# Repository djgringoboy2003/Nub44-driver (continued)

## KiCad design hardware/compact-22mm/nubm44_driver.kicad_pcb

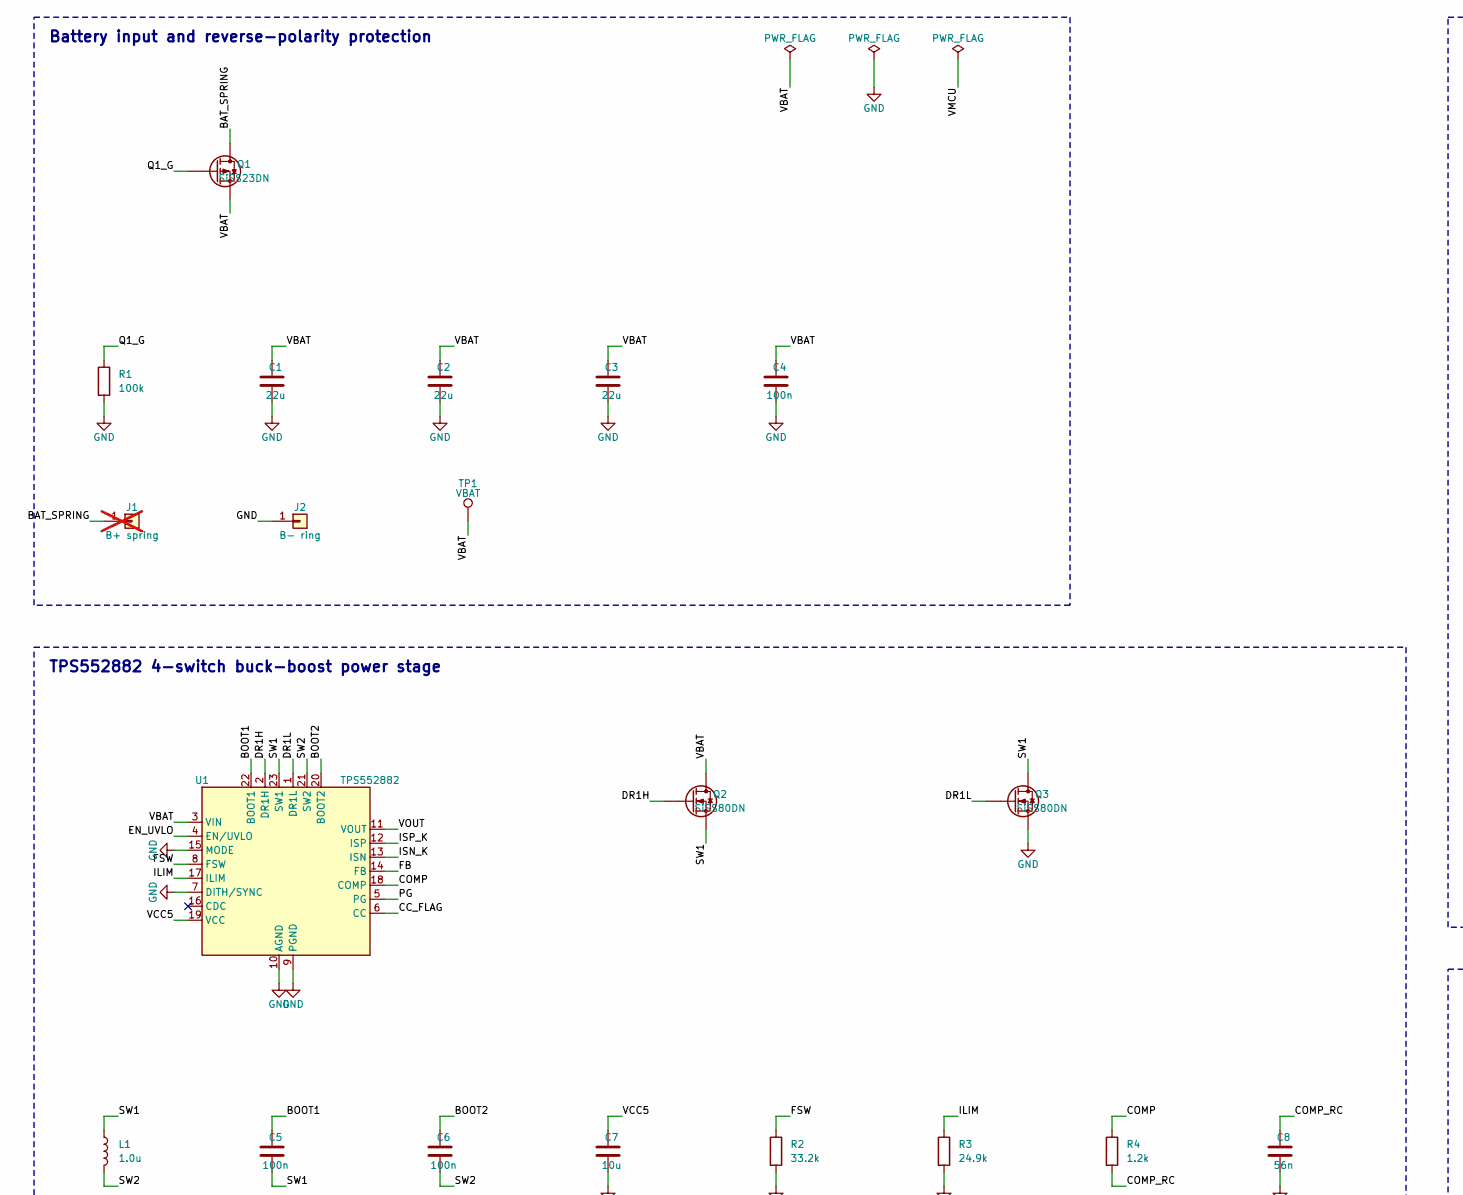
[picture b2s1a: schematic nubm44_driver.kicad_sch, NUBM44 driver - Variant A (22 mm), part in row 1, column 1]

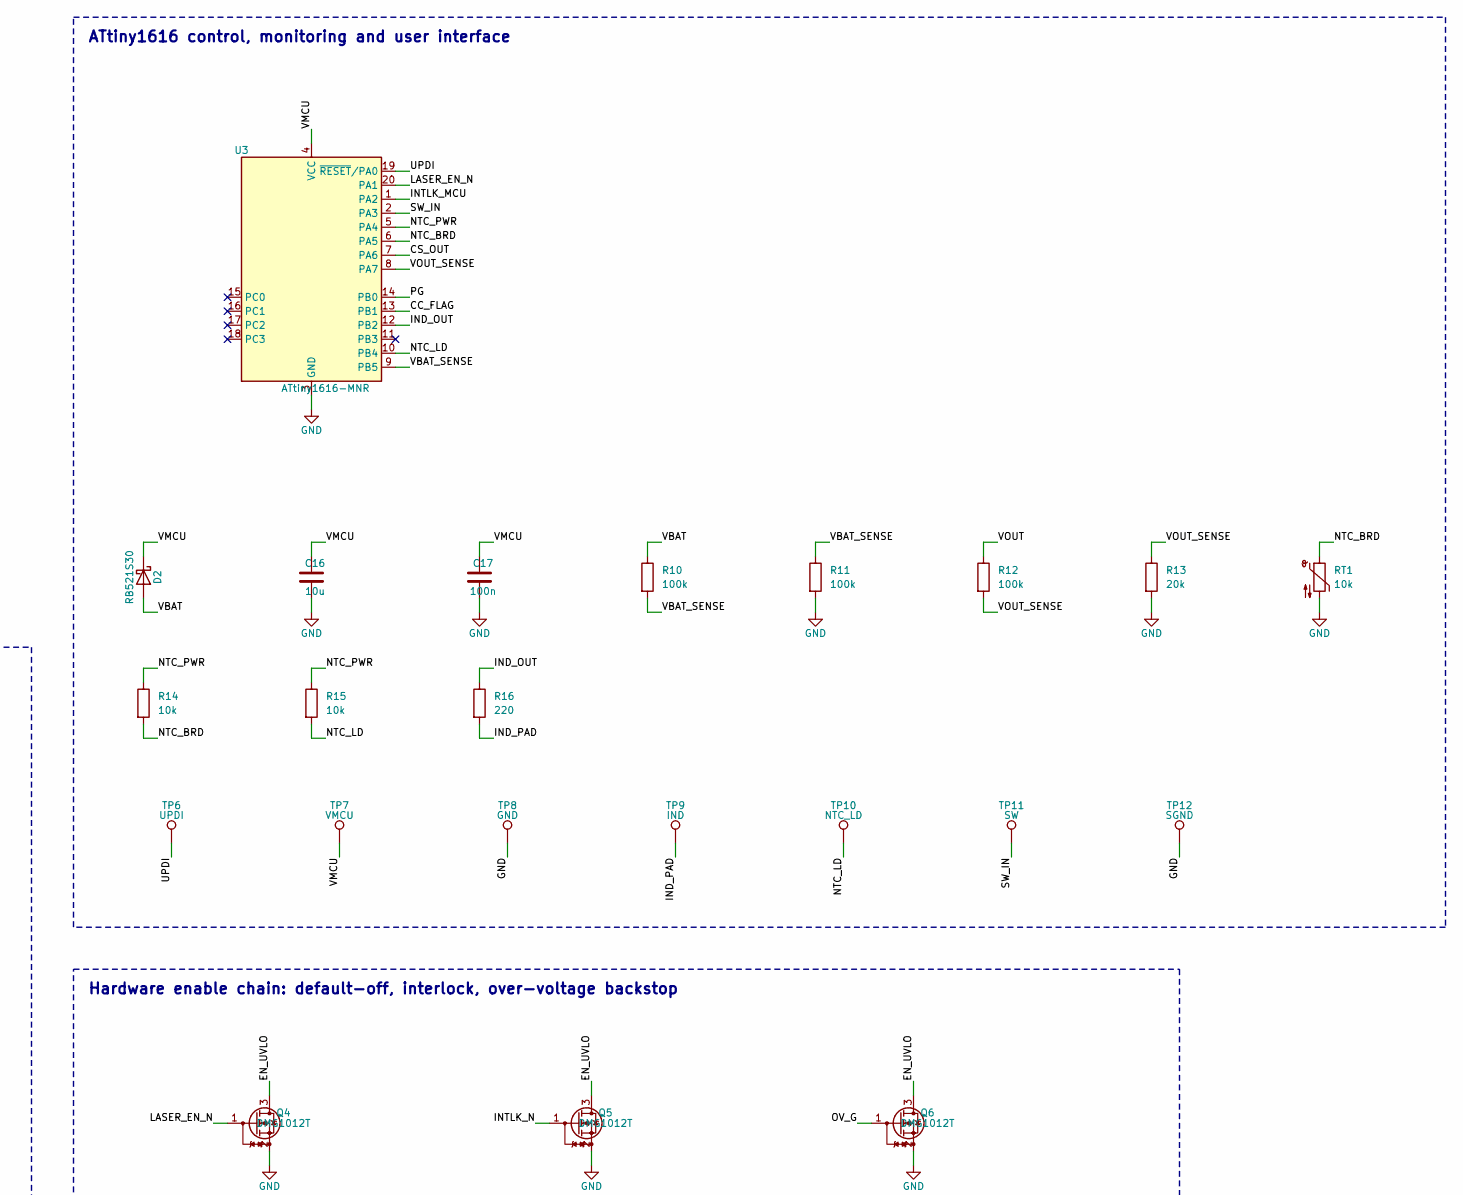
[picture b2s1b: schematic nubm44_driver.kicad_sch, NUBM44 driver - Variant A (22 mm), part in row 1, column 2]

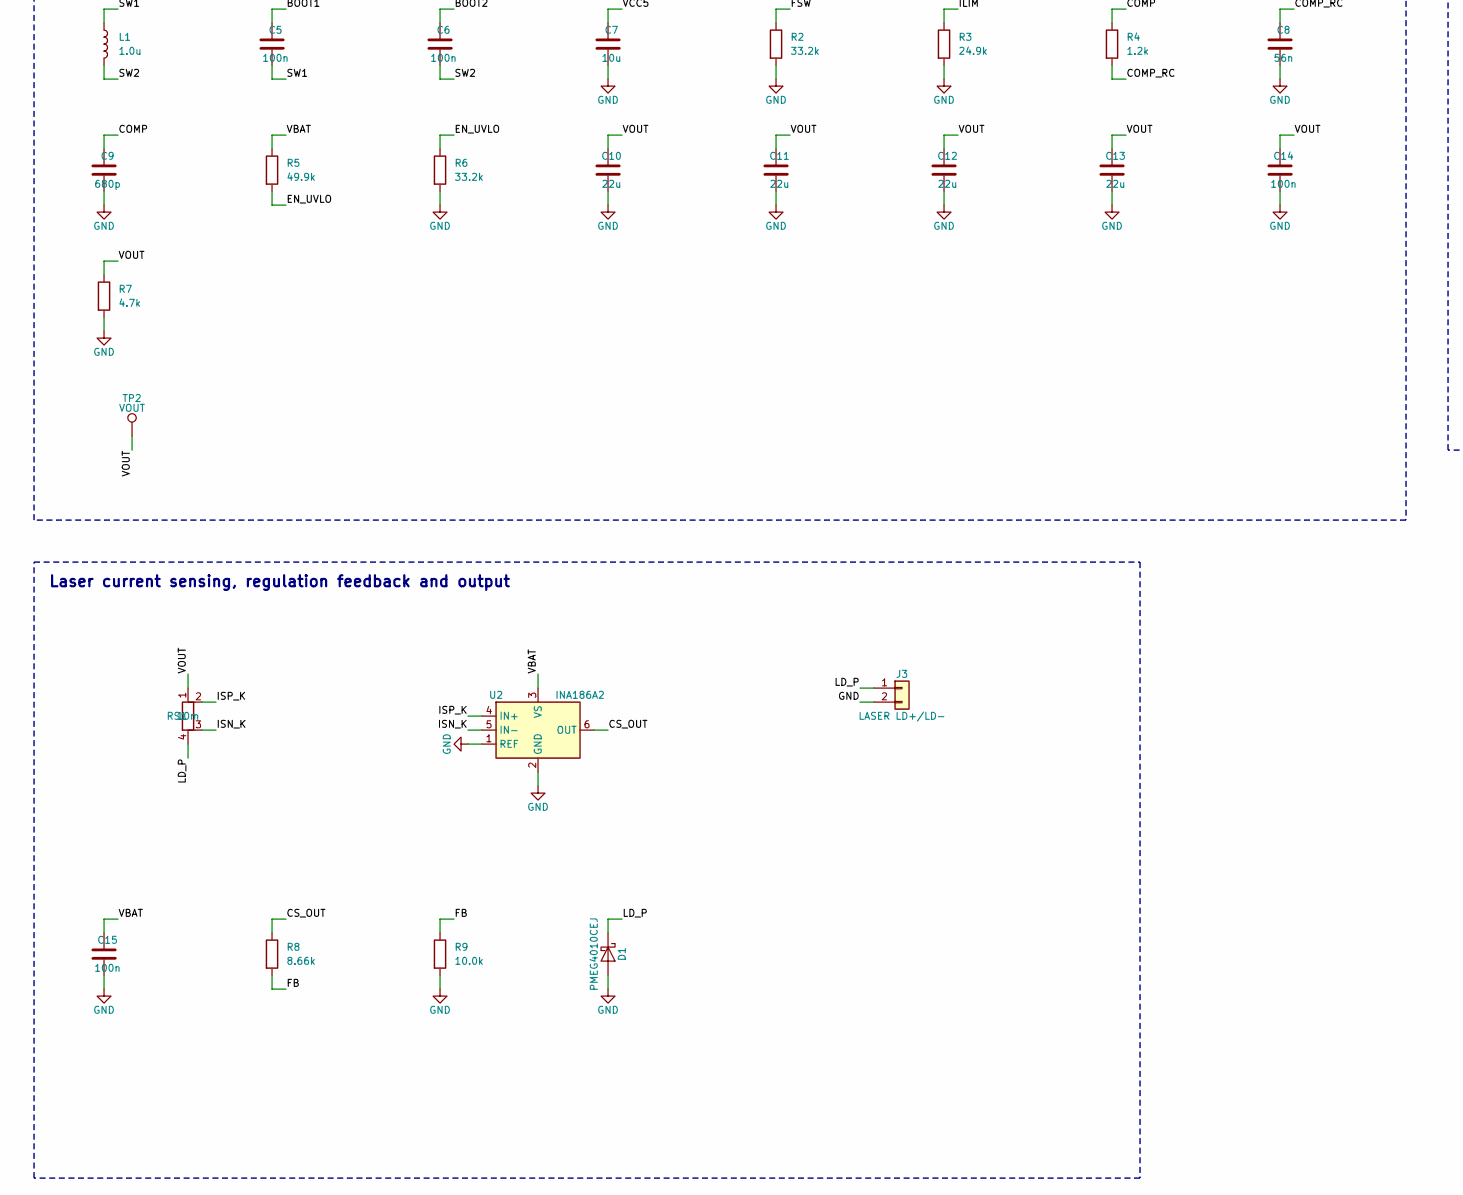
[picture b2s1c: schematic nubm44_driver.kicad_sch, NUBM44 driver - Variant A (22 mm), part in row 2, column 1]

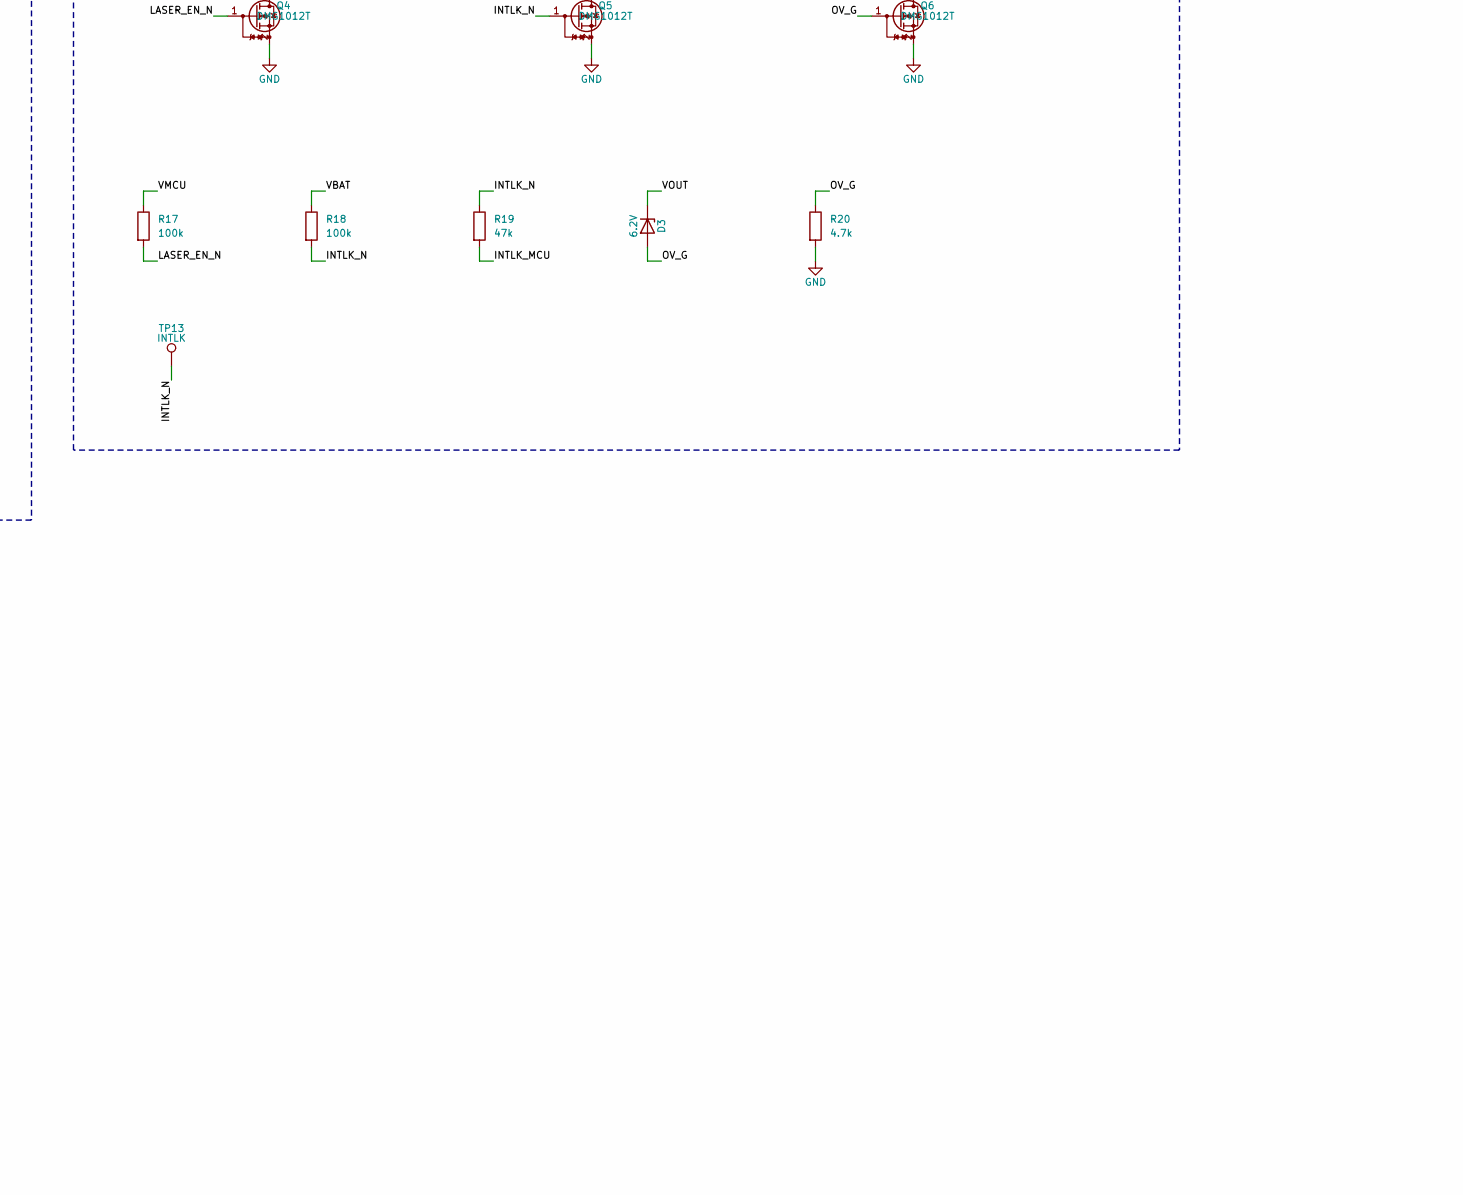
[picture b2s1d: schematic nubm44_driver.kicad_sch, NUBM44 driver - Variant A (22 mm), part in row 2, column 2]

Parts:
C1, C2, C3, C10, C11, C12, C13: 22u; C_0805_2012Metric; MPN CL21A226MOQNNNE
C4, C5, C6, C14, C15, C17: 100n; C_0201_0603Metric; MPN GRM033R61A104KE15D
C7, C16: 10u; C_0603_1608Metric; MPN CL10A106KP8NNNC
C8: 56n; C_0402_1005Metric; MPN CL05B563KO5NNNC
C9: 680p; C_0201_0603Metric; MPN GRM0335C1H681JA01D
D1: PMEG4010CEJ; D_SOD-323F; MPN PMEG4010CEJ,115
D2: RB521S30; D_SOD-523; MPN RB521S30T1G
D3: 6.2V; D_SOD-523; MPN BZX585-C6V2
J1: B+ spring; Contact_Spring_Pad_D5.0mm; MPN UNKNOWN; not fitted
J2: B- ring; Contact_Ring_R10.20_W0.80mm
J3: LASER LD+/LD-; Laser_Pads_2x_PTH_P3.5mm_D1.1mm
L1: 1.0u; L_Coilcraft_XAL5030-XXX; MPN XGL5030-102MEC
Q1: SiSS23DN; Vishay_PowerPAK_1212-8_Single; MPN SISS23DN-T1-GE3
Q2, Q3: SiSS80DN; Vishay_PowerPAK_1212-8_Single; MPN SISS80DN-T1-GE3
Q4, Q5, Q6: DMG1012T; SOT-523; MPN DMG1012T-7
R1, R10, R11, R12, R17, R18: 100k; R_0201_0603Metric; MPN RC0201FR-07100KL
R2, R6: 33.2k; R_0201_0603Metric; MPN RC0201FR-0733K2L
R3: 24.9k; R_0201_0603Metric; MPN RC0201FR-0724K9L
R4: 1.2k; R_0201_0603Metric; MPN RC0201FR-071K2L
R5: 49.9k; R_0201_0603Metric; MPN RC0201FR-0749K9L
R7, R20: 4.7k; R_0201_0603Metric; MPN RC0201FR-074K7L
R8: 8.66k; R_0402_1005Metric; MPN RT0402BRD078K66L
R9: 10.0k; R_0402_1005Metric; MPN RT0402BRD0710KL
R13: 20k; R_0201_0603Metric; MPN RC0201FR-0720KL
R14, R15: 10k; R_0201_0603Metric; MPN RC0201FR-0710KL
R16: 220; R_0201_0603Metric; MPN RC0201FR-07220RL
R19: 47k; R_0201_0603Metric; MPN RC0201FR-0747KL
RS1: 10m; R_1206_3216Metric_Kelvin; MPN MCS1632R010FER
RT1: 10k; R_0201_0603Metric; MPN NCP03XH103F05RL
TP1: VBAT; Pad_SMD_D0.8mm_B
TP2: VOUT; Pad_SMD_D0.8mm_B
TP6: UPDI; Pad_SMD_D0.8mm_B
TP7: VMCU; Pad_SMD_D0.8mm_B
TP8: GND; Pad_SMD_D0.8mm_B
TP9: IND; Pad_SMD_D1.0mm_F
TP10: NTC_LD; Pad_SMD_D1.0mm_F
TP11: SW; Pad_SMD_D1.0mm_F
TP12: SGND; Pad_SMD_D1.0mm_F
TP13: INTLK; Pad_SMD_D1.0mm_F
U1: TPS552882; TI_RPM0026A_VQFN-HR-26_4x3.5mm_P0.5mm; MPN TPS552882RPMR
U2: INA186A2; SOT-363_SC-70-6; MPN INA186A2IDCKR
U3: ATtiny1616-MNR; VQFN-20-1EP_3x3mm_P0.4mm_EP1.7x1.7mm; MPN ATTINY1616-MNR

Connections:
/BAT_SPRING: J1.1, Q1.5 (D)
/BOOT1: C5.1, U1.22 (BOOT1)
/BOOT2: C6.1, U1.20 (BOOT2)
/CC_FLAG: U1.6 (CC), U3.13 (PB1)
/COMP: C9.1, R4.1, U1.18 (COMP)
/COMP_RC: C8.1, R4.2
/CS_OUT: R8.1, U2.6 (OUT), U3.7 (PA6)
/DR1H: Q2.4 (G), U1.2 (DR1H)
/DR1L: Q3.4 (G), U1.1 (DR1L)
/EN_UVLO: Q4.3 (D), Q5.3 (D), Q6.3 (D), R5.2, R6.1, U1.4 (EN/UVLO)
/FB: R8.2, R9.1, U1.14 (FB)
/FSW: R2.1, U1.8 (FSW)
/ILIM: R3.1, U1.17 (ILIM)
/IND_OUT: R16.1, U3.12 (PB2)
/IND_PAD: R16.2, TP9.1
/INTLK_MCU: R19.2, U3.1 (PA2)
/INTLK_N: Q5.1 (G), R18.2, R19.1, TP13.1
/ISN_K: RS1.3, U1.13 (ISN), U2.5 (IN-)
/ISP_K: RS1.2, U1.12 (ISP), U2.4 (IN+)
/LASER_EN_N: Q4.1 (G), R17.2, U3.20 (PA1)
/LD_P: D1.1 (K), J3.1, RS1.4
/NTC_BRD: R14.2, RT1.1, U3.6 (PA5)
/NTC_LD: R15.2, TP10.1, U3.10 (PB4)
/NTC_PWR: R14.1, R15.1, U3.5 (PA4)
/OV_G: D3.2 (A), Q6.1 (G), R20.1
/PG: U1.5 (PG), U3.14 (PB0)
/Q1_G: Q1.4 (G), R1.1
/SW1: C5.2, L1.1, Q2.1 (S), Q2.2 (S), Q2.3 (S), Q3.5 (D), U1.23 (SW1)
/SW2: C6.2, L1.2, U1.21 (SW2), U1.25 (SW2)
/SW_IN: TP11.1, U3.2 (PA3)
/UPDI: TP6.1, U3.19 (~RESET/PA0)
/VBAT: C1.1, C2.1, C3.1, C4.1, C15.1, D2.2 (A), Q1.1 (S), Q1.2 (S), Q1.3 (S), Q2.5 (D), R5.1, R10.1, R18.1, TP1.1, U1.3 (VIN), U2.3 (VS)
/VBAT_SENSE: R10.2, R11.1, U3.9 (PB5)
/VCC5: C7.1, U1.19 (VCC)
/VMCU: C16.1, C17.1, D2.1 (K), R17.1, TP7.1, U3.4 (VCC)
/VOUT: C10.1, C11.1, C12.1, C13.1, C14.1, D3.1 (K), R7.1, R12.1, RS1.1, TP2.1, U1.11 (VOUT), U1.26 (VOUT)
/VOUT_SENSE: R12.2, R13.1, U3.8 (PA7)
GND: C1.2, C2.2, C3.2, C4.2, C7.2, C8.2, C9.2, C10.2, C11.2, C12.2, C13.2, C14.2, C15.2, C16.2, C17.2, D1.2 (A), J2.1, J3.2, Q3.1 (S), Q3.2 (S), Q3.3 (S), Q4.2 (S), Q5.2 (S), Q6.2 (S), R1.2, R2.2, R3.2, R6.2, R7.2, R9.2, R11.2, R13.2, R20.2, RT1.2, TP8.1, TP12.1, U1.7 (DITH/SYNC), U1.9 (PGND), U1.10 (AGND), U1.15 (MODE), U1.24 (PGND), U2.1 (REF), U2.2 (GND), U3.3 (GND), U3.21 (GND)

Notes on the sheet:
Battery input and reverse-polarity protection
Laser current sensing, regulation feedback and output
Hardware enable chain: default-off, interlock, over-voltage backstop
TPS552882 4-switch buck-boost power stage
ATtiny1616 control, monitoring and user interface

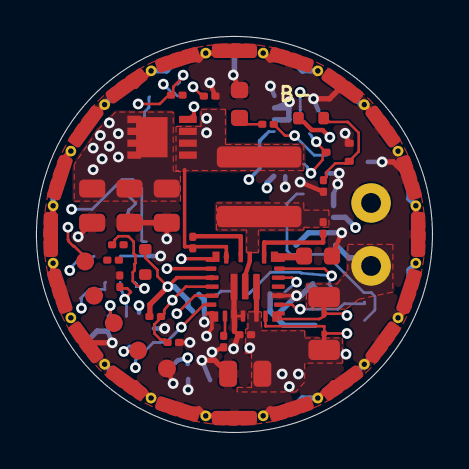
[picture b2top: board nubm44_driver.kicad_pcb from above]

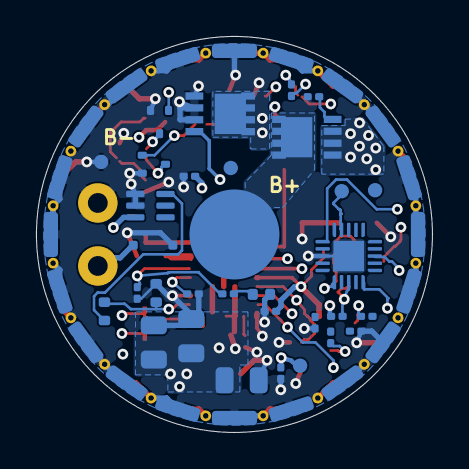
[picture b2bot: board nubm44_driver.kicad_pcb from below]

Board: 4 copper layers, 22.0 x 22.0 mm, 65 parts (32 on the bottom side), 38 nets.

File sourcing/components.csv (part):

variant,reference_designators,quantity,manufacturer,mpn,value,tolerance,voltage_rating,current_rating,power_rating,package,footprint,datasheet,preferred_supplier,supplier_part_number,availability,approx_price_usd,data_retrieved,verified,approved_alternatives,notes
compact-22mm,J1,1,UNKNOWN,UNKNOWN,B+ spring,UNKNOWN,UNKNOWN,UNKNOWN,UNKNOWN,Contact_Spring_Pad_D5.0mm,nubm44:Contact_Spring_Pad_D5.0mm,~,UNKNOWN,UNKNOWN,UNKNOWN,UNKNOWN,-,NO,-,"DNP: hand-fitted battery spring, select to suit host"
compact-22mm,Q1,1,Vishay,SISS23DN-T1-GE3,SiSS23DN,Rds 6.3 mOhm max @ -2.5 V,-20 V,see datasheet,-,Vishay_PowerPAK_1212-8_Single,Package_SO:Vishay_PowerPAK_1212-8_Single,https://www.vishay.com/docs/62999/siss23dn.pdf,LCSC,C222439,220,1+: $1.8603 / 10+: $1.5797,2026-10-24,YES,Diodes Inc. DMP2005UFG-13,
compact-22mm,"R1,R10,R11,R12,R17,R18",6,Yageo,RC0201FR-07100KL,100k,+-1 %,25 V,-,1/20 W,R_0201_0603Metric,Resistor_SMD:R_0201_0603Metric,~,UNKNOWN,UNKNOWN,UNKNOWN,UNKNOWN,-,NO,-,"commodity part: supplier data not verified, choose an equivalent at order time"
compact-22mm,"C1,C2,C3,C10,C11,C12,C13",7,Samsung,CL21A226MOQNNNE,22u,+-20 % X5R,16 V,-,-,C_0805_2012Metric,Capacitor_SMD:C_0805_2012Metric,~,LCSC,C98190,19970,10+: $0.0916 / 100+: $0.0739,2026-10-24,PARTIAL,-,
compact-22mm,"C4,C5,C6,C14,C15,C17",6,Murata,GRM033R61A104KE15D,100n,+-10 % X5R,10 V,-,-,C_0201_0603Metric,Capacitor_SMD:C_0201_0603Metric,~,UNKNOWN,UNKNOWN,UNKNOWN,UNKNOWN,-,NO,-,"commodity part: supplier data not verified, choose an equivalent at order time"
compact-22mm,U1,1,Texas Instruments,TPS552882RPMR,TPS552882,VREF +-1 %,"VIN 2.7-36 V, VOUT 0.8-22 V",14 A min avg inductor limit (RILIM 20k),-,TI_RPM0026A_VQFN-HR-26_4x3.5mm_P0.5mm,nubm44:TI_RPM0026A_VQFN-HR-26_4x3.5mm_P0.5mm,https://www.ti.com/lit/ds/symlink/tps552882.pdf,TI store,TPS552882RPMR,"2950 (TI store, 2026-10-24, PWR-20)",UNKNOWN,2026-10-24,PARTIAL,-,
compact-22mm,"Q2,Q3",2,Vishay,SISS80DN-T1-GE3,SiSS80DN,Rds 1.15 mOhm max @ 4.5 V,20 V,see datasheet,-,Vishay_PowerPAK_1212-8_Single,Package_SO:Vishay_PowerPAK_1212-8_Single,https://www.vishay.com/docs/77684/siss80dn.pdf,UNKNOWN,UNKNOWN,UNKNOWN,UNKNOWN,-,NO,Diodes Inc. DMN22M5UFG-7; Infineon IRLHM620TRPBF,"commodity part: supplier data not verified, choose an equivalent at order time"
compact-22mm,L1,1,Coilcraft,XGL5030-102MEC,1.0u,+-20 %,-,"Isat 10.2 A (20 %) / 14 A (30 %), Irms 12.8 A",-,L_Coilcraft_XAL5030-XXX,Inductor_SMD:L_Coilcraft_XAL5030-XXX,~,LCSC / Coilcraft,C6937849,UNKNOWN,UNKNOWN,2026-10-24,PARTIAL,Coilcraft XAL5030-102MEC,
compact-22mm,"C7,C16",2,Samsung,CL10A106KP8NNNC,10u,+-10 % X5R,10 V,-,-,C_0603_1608Metric,Capacitor_SMD:C_0603_1608Metric,~,UNKNOWN,UNKNOWN,UNKNOWN,UNKNOWN,-,NO,-,"commodity part: supplier data not verified, choose an equivalent at order time"
compact-22mm,"R2,R6",2,Yageo,RC0201FR-0733K2L,33.2k,+-1 %,25 V,-,1/20 W,R_0201_0603Metric,Resistor_SMD:R_0201_0603Metric,~,UNKNOWN,UNKNOWN,UNKNOWN,UNKNOWN,-,NO,-,"commodity part: supplier data not verified, choose an equivalent at order time"
compact-22mm,R3,1,Yageo,RC0201FR-0724K9L,24.9k,+-1 %,25 V,-,1/20 W,R_0201_0603Metric,Resistor_SMD:R_0201_0603Metric,~,UNKNOWN,UNKNOWN,UNKNOWN,UNKNOWN,-,NO,-,"commodity part: supplier data not verified, choose an equivalent at order time"
compact-22mm,R4,1,Yageo,RC0201FR-071K2L,1.2k,+-1 %,25 V,-,1/20 W,R_0201_0603Metric,Resistor_SMD:R_0201_0603Metric,~,UNKNOWN,UNKNOWN,UNKNOWN,UNKNOWN,-,NO,-,"commodity part: supplier data not verified, choose an equivalent at order time"
compact-22mm,C8,1,Samsung,CL05B563KO5NNNC,56n,+-10 % X7R,16 V,-,-,C_0402_1005Metric,Capacitor_SMD:C_0402_1005Metric,~,UNKNOWN,UNKNOWN,UNKNOWN,UNKNOWN,-,NO,-,"commodity part: supplier data not verified, choose an equivalent at order time"
compact-22mm,C9,1,Murata,GRM0335C1H681JA01D,680p,+-5 % C0G,50 V,-,-,C_0201_0603Metric,Capacitor_SMD:C_0201_0603Metric,~,UNKNOWN,UNKNOWN,UNKNOWN,UNKNOWN,-,NO,-,"commodity part: supplier data not verified, choose an equivalent at order time"
compact-22mm,R5,1,Yageo,RC0201FR-0749K9L,49.9k,+-1 %,25 V,-,1/20 W,R_0201_0603Metric,Resistor_SMD:R_0201_0603Metric,~,UNKNOWN,UNKNOWN,UNKNOWN,UNKNOWN,-,NO,-,"commodity part: supplier data not verified, choose an equivalent at order time"
compact-22mm,"R7,R20",2,Yageo,RC0201FR-074K7L,4.7k,+-1 %,25 V,-,1/20 W,R_0201_0603Metric,Resistor_SMD:R_0201_0603Metric,~,UNKNOWN,UNKNOWN,UNKNOWN,UNKNOWN,-,NO,-,"commodity part: supplier data not verified, choose an equivalent at order time"
compact-22mm,RS1,1,Ohmite,MCS1632R010FER,10m,+-1 %,-,-,1 W,R_1206_3216Metric_Kelvin,nubm44:R_1206_3216Metric_Kelvin,~,DigiKey,MCS1632R010FER,UNKNOWN,UNKNOWN,2026-10-24,PARTIAL,RALEC LR1206-21R010F4,
compact-22mm,U2,1,Texas Instruments,INA186A2IDCKR,INA186A2,"gain +-1 %, VOS +-50 uV","VS 1.7-5.5 V, VCM -0.2..40 V",-,-,SOT-363_SC-70-6,Package_TO_SOT_SMD:SOT-363_SC-70-6,https://www.ti.com/lit/ds/symlink/ina186.pdf,LCSC,C2058238,9836,1+: $0.8667 / 10+: $0.691,2026-10-24,YES,Texas Instruments INA186A3IDCKR,
compact-22mm,R8,1,Yageo,RT0402BRD078K66L,8.66k,"+-0.1 %, 25 ppm/K",50 V,-,1/16 W,R_0402_1005Metric,Resistor_SMD:R_0402_1005Metric,~,UNKNOWN,UNKNOWN,UNKNOWN,UNKNOWN,-,NO,-,"commodity part: supplier data not verified, choose an equivalent at order time"
compact-22mm,R9,1,Yageo,RT0402BRD0710KL,10.0k,"+-0.1 %, 25 ppm/K",50 V,-,1/16 W,R_0402_1005Metric,Resistor_SMD:R_0402_1005Metric,~,UNKNOWN,UNKNOWN,UNKNOWN,UNKNOWN,-,NO,-,"commodity part: supplier data not verified, choose an equivalent at order time"
compact-22mm,D1,1,Nexperia,"PMEG4010CEJ,115",PMEG4010CEJ,-,40 V,1 A,-,D_SOD-323F,Diode_SMD:D_SOD-323F,~,LCSC,C50704,16100,5+: $0.3702 / 50+: $0.2953,2026-10-24,PARTIAL,-,
compact-22mm,U3,1,Microchip,ATTINY1616-MNR,ATtiny1616-MNR,-,1.8-5.5 V,-,-,VQFN-20-1EP_3x3mm_P0.4mm_EP1.7x1.7mm,Package_DFN_QFN:VQFN-20-1EP_3x3mm_P0.4mm_EP1.7x1.7mm,https://ww1.microchip.com/downloads/en/DeviceDoc/ATtiny1614-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,LCSC,C507118,3507,1+: $1.0962 / 10+: $0.908,2026-10-24,YES,-,
compact-22mm,D2,1,onsemi,RB521S30T1G,RB521S30,-,30 V,200 mA,-,D_SOD-523,Diode_SMD:D_SOD-523,~,UNKNOWN,UNKNOWN,UNKNOWN,UNKNOWN,-,NO,-,"commodity part: supplier data not verified, choose an equivalent at order time"
compact-22mm,R13,1,Yageo,RC0201FR-0720KL,20k,+-1 %,25 V,-,1/20 W,R_0201_0603Metric,Resistor_SMD:R_0201_0603Metric,~,UNKNOWN,UNKNOWN,UNKNOWN,UNKNOWN,-,NO,-,"commodity part: supplier data not verified, choose an equivalent at order time"
compact-22mm,RT1,1,Murata,NCP03XH103F05RL,10k,"+-1 %, B 3380 K",-,-,-,R_0201_0603Metric,Resistor_SMD:R_0201_0603Metric,~,UNKNOWN,UNKNOWN,UNKNOWN,UNKNOWN,-,NO,-,"commodity part: supplier data not verified, choose an equivalent at order time"
compact-22mm,"R14,R15",2,Yageo,RC0201FR-0710KL,10k,+-1 %,25 V,-,1/20 W,R_0201_0603Metric,Resistor_SMD:R_0201_0603Metric,~,UNKNOWN,UNKNOWN,UNKNOWN,UNKNOWN,-,NO,-,"commodity part: supplier data not verified, choose an equivalent at order time"
compact-22mm,R16,1,Yageo,RC0201FR-07220RL,220,+-1 %,25 V,-,1/20 W,R_0201_0603Metric,Resistor_SMD:R_0201_0603Metric,~,UNKNOWN,UNKNOWN,UNKNOWN,UNKNOWN,-,NO,-,"commodity part: supplier data not verified, choose an equivalent at order time"
compact-22mm,"Q4,Q5,Q6",3,Diodes Incorporated,DMG1012T-7,DMG1012T,-,20 V,0.63 A,-,SOT-523,Package_TO_SOT_SMD:SOT-523,~,LCSC,C20512,124900,5+: $0.1019 / 50+: $0.0837,2026-10-24,YES,-,
compact-22mm,R19,1,Yageo,RC0201FR-0747KL,47k,+-1 %,25 V,-,1/20 W,R_0201_0603Metric,Resistor_SMD:R_0201_0603Metric,~,UNKNOWN,UNKNOWN,UNKNOWN,UNKNOWN,-,NO,-,"commodity part: supplier data not verified, choose an equivalent at order time"
compact-22mm,D3,1,Nexperia,BZX585-C6V2,6.2V,+-5 %,6.2 V Zener,-,300 mW,D_SOD-523,Diode_SMD:D_SOD-523,~,UNKNOWN,UNKNOWN,UNKNOWN,UNKNOWN,-,NO,-,"commodity part: supplier data not verified, choose an equivalent at order time"
evaluation-board,J1,1,UNKNOWN,UNKNOWN,B+ spring,UNKNOWN,UNKNOWN,UNKNOWN,UNKNOWN,Wire_Pad_PTH_D1.3mm,nubm44:Wire_Pad_PTH_D1.3mm,~,UNKNOWN,UNKNOWN,UNKNOWN,UNKNOWN,-,NO,-,"DNP: hand-fitted battery spring, select to suit host"
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
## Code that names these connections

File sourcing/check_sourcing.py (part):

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    "CS_OUT": (2.6, V_BAT, "0.5 V/A at the 5.2 A ceiling; fault: INA186 output at its VBAT supply"),
    "FB": (1.3, V_BAT, "1.2 V regulation"), "COMP": (2.5, V_VCC, "COMP clamp"), "COMP_RC": (2.5, V_VCC, "COMP clamp"),
    "VBAT_SENSE": (V_BAT / 2, V_BAT, "VBAT/2"), "VOUT_SENSE": (V_OUT_NORMAL / 6, V_OUT_FAULT, "VOUT/6"),
    "NTC_PWR": (V_BAT, V_BAT, "MCU pin at VMCU"), "NTC_BRD": (V_BAT, V_BAT, "MCU pin"), "NTC_LD": (V_BAT, V_BAT, "MCU pin"),
    "IND_OUT": (V_BAT, V_BAT, "MCU pin"), "IND_PAD": (V_BAT, V_BAT, "external LED pad"),
    "LASER_EN_N": (V_BAT, V_BAT, "MCU pin / R17"), "INTLK_N": (V_BAT, V_BAT, "R18 pull-up to VBAT"),
    "INTLK_MCU": (V_BAT, V_BAT, "MCU pin"), "OV_G": (V_OUT_FAULT - 6.2, V_OUT_FAULT, "Zener D3 6.2 V below VOUT"),
    "FSW": (1.0, V_VCC, "1.0 V pin"), "ILIM": (0.6, V_VCC, "0.6 V pin"),
}
# voltage across two-terminal parts whose terminals are both non-ground
PAIR_V = {frozenset(("BOOT1", "SW1")): (V_VCC, V_VCC, "bootstrap: VCC across the capacitor"),
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
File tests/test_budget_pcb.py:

"""Budget-2s placement source stays consistent with its connectivity and design decisions."""
from __future__ import annotations

import json
import sys
from pathlib import Path

import pytest
import yaml

ROOT = Path(__file__).resolve().parents[1]
sys.path.insert(0, str(ROOT / "automation"))
from nubm44 import evidence  # noqa: E402
from nubm44.variants import sources_for  # noqa: E402

SRC = sources_for("budget-2s")
PLACE = yaml.safe_load(SRC.placement.read_text(encoding="utf-8"))
PARTS = {p["ref"]: p for p in yaml.safe_load(SRC.connectivity.read_text(encoding="utf-8"))["parts"]}


def test_every_part_has_exactly_one_placement_entry():
    assert set(PLACE["parts"]) == set(PARTS)


def test_manual_positions_and_pours_lie_inside_the_board():
    w, h = PLACE["board"]["outline"]["w"] / 2, PLACE["board"]["outline"]["h"] / 2
    for ref, cfg in PLACE["parts"].items():
        x, y = (cfg["pos"][:2] if "pos" in cfg else cfg["auto"]["anchor"])
        assert abs(x) < w and abs(y) < h, ref
    for z in PLACE["zones_pre"] + PLACE["zones_post"]:
        assert all(abs(x) <= w + 0.6 and abs(y) <= h + 0.6 for x, y in z["polygon"]), z["net"]


def test_kelvin_traces_start_on_the_shunt_pads_and_carry_the_right_nets():
    rs1 = PLACE["parts"]["RS1"]["pos"]
    pad1, pad2 = (rs1[0] - 2.96, rs1[1]), (rs1[0] + 2.96, rs1[1])  # R_2512_6332Metric pads, 1.23 x 3.35 mm
    first = {}
    for t in PLACE["tracks"]:
        if "kelvin" in t:
            first.setdefault((t["kelvin"], t["net"]), t)  # a chain starts with its first listed segment
    # separate pairs for INA186 (U2) and INA300 (U3)
    assert set(first) == {(u, n) for u in ("U2", "U3") for n in ("VBUCK", "VSH")}
    for (_, net), t in first.items():
        cx, cy = pad1 if net == "VBUCK" else pad2
        sx, sy = t["pts"][0]
        assert abs(sx - cx) <= 0.615 and abs(sy - cy) <= 1.675, t
    assert {PARTS["U2"]["pins"][4], PARTS["U2"]["pins"][5]} == {"VBUCK", "VSH"}
    assert {PARTS["U3"]["pins"][1], PARTS["U3"]["pins"][2]} == {"VBUCK", "VSH"}


def test_battery_polarity_text_is_beside_the_matching_xt30_pad():
    x, y, rot = PLACE["parts"]["J1"]["pos"]
    assert rot == 90 and PARTS["J1"]["pins"] == {1: "GND", 2: "VBAT_IN"}
    pad2_y = y + 5.0  # footprint pad 2 at (-5, 0) rotated 90 degrees counter-clockwise
    texts = {t["text"]: t["at"] for t in PLACE["texts"]}
    assert abs(texts["B+"][1] - pad2_y) < abs(texts["B-"][1] - pad2_y)


def test_u1_paste_apertures_keep_clear_of_the_thermal_via_drills():
    import importlib.util  # by path: automation/setup/build_library.py (A/B) shares the module name
    spec = importlib.util.spec_from_file_location("budget_build_library", ROOT / "automation/budget/build_library.py")
    build_library = importlib.util.module_from_spec(spec)
    spec.loader.exec_module(build_library)
    fp = build_library.tps54821_rhl0014a()
    pads = [n for n in fp if isinstance(n, list) and n and str(n[0]) == "pad"]
    drills = [next(float(c[1]) for c in p if isinstance(c, list) and str(c[0]) == "drill") for p in pads
              if str(p[2]) == "thru_hole"]
    vias = [next((float(c[1]), float(c[2])) for c in p if isinstance(c, list) and str(c[0]) == "at") for p in pads
            if str(p[2]) == "thru_hole"]
    paste = []
    for p in pads:
        layers = next(c for c in p if isinstance(c, list) and str(c[0]) == "layers")
        if [str(x) for x in layers[1:]] == ["F.Paste"]:
            at = next(c for c in p if isinstance(c, list) and str(c[0]) == "at")
            size = next(c for c in p if isinstance(c, list) and str(c[0]) == "size")
            paste.append((float(at[1]), float(at[2]), float(size[1]), float(size[2])))
    assert len(vias) == 5 and len(paste) == 8
    for (vx, vy), d in zip(vias, drills):
        for x, y, w, h in paste:  # distance from the drill centre to the nearest point of the aperture
            dx, dy = max(abs(vx - x) - w / 2, 0.0), max(abs(vy - y) - h / 2, 0.0)
            assert (dx * dx + dy * dy) ** 0.5 >= d / 2 + 0.05 - 1e-9, ((vx, vy), (x, y))


def test_layout_review_when_present_is_current_and_within_allocation():
    ev = ROOT / "reports/budget-2s/layout-review-evidence.json"
    if not ev.exists():
        pytest.skip("budget layout review not run")
    assert not evidence.problems(evidence.load(ev), expected_kind="budget-layout-review")
    s = json.loads((ROOT / "reports/budget-2s/layout-review.json").read_text(encoding="utf-8"))["summary"]
    assert s["output_ok"] and s["input_ok"]


def test_bom_never_merges_different_tolerances_or_part_types():
    bom = ROOT / "manufacturing/budget-2s/assembly/BOM.csv"
    if not bom.exists():
        pytest.skip("budget export not run")
    import csv
    rows = list(csv.DictReader(bom.read_text(encoding="utf-8-sig").splitlines()))
    for r in rows:
        notes = r["Requirement / notes"]
        assert not ("0.1%" in notes and " 1% " in notes), r["Designators"]
        refs = r["Designators"].split(",")
        assert not ({"TH1"} & set(refs) and len(refs) > 1), r["Designators"]
    placed = {ref for r in rows for ref in r["Designators"].split(",")}
    assert placed == {ref for ref, p in PARTS.items() if p.get("in_bom", True)}


def test_every_bom_part_has_an_mpn_and_exactly_one_sourcing_entry():
    import re
    sourcing = yaml.safe_load((ROOT / "engineering/design/budget-2s/sourcing.yaml").read_text(encoding="utf-8"))
    bom = {p["ref"]: p for p in PARTS.values() if p.get("in_bom", True)}
    assert not [r for r, p in bom.items() if str(p.get("mpn", "UNKNOWN")) in ("", "UNKNOWN")]
    entries = {str(m): c for m, c in sourcing["parts"].items()}
    assert set(entries) == {str(p["mpn"]) for p in bom.values()}
    for mpn, c in entries.items():
        assert c.get("evidence"), mpn
        assert c["lcsc"] == "UNKNOWN" or re.fullmatch(r"C\d+", c["lcsc"]), mpn
        assert c.get("jlc", "Basic") in ("Basic", "Extended"), mpn
        eq = c.get("lcsc_equivalent")
        if eq:  # only for a part LCSC does not list, and always with its own MPN, maker, code and evidence
            assert c["lcsc"] == "UNKNOWN" and eq["mpn"] != mpn and eq.get("mfr") and eq.get("evidence"), mpn
            assert re.fullmatch(r"C\d+", eq["lcsc"]), mpn
    # the 0.1 % / 25 ppm lines are never satisfied by Yageo RT/AT...BRE (+-50 ppm/C) parts, nor by their equivalents
    precision = [p for p in bom.values() if "0.1%" in p.get("desc", "")]
    chosen = [(p["ref"], m) for p in precision
              for m in (str(p["mpn"]), entries[str(p["mpn"])].get("lcsc_equivalent", {}).get("mpn", ""))]
    assert precision and not [c for c in chosen if re.match(r"(RT|AT)\d{4}BRE", c[1])]


def test_jlcpcb_bom_names_and_codes_the_lcsc_equivalent_never_the_unlisted_part():
    bom = ROOT / "manufacturing/budget-2s/assembly/BOM_JLCPCB.csv"
    if not bom.exists():
        pytest.skip("budget export not run")
    import csv
    sourcing = yaml.safe_load((ROOT / "engineering/design/budget-2s/sourcing.yaml").read_text(encoding="utf-8"))
    rows = {r["Designator"]: r for r in csv.DictReader(bom.read_text(encoding="utf-8-sig").splitlines())}
    checked = 0
    for mpn, c in sourcing["parts"].items():
        eq = c.get("lcsc_equivalent")
        refs = {r for r, p in PARTS.items() if str(p.get("mpn")) == str(mpn) and p.get("in_bom", True)}
        mine = [v for k, v in rows.items() if set(k.split(",")) <= refs]  # one MPN may span several BOM lines
        assert mine and {r for v in mine for r in v["Designator"].split(",")} == refs, mpn
        for row in mine:
            if eq:
                assert row["LCSC Part #"] == eq["lcsc"] and eq["mpn"] in row["Comment"], mpn
                assert str(mpn) not in row["Comment"], mpn
            else:
                assert row["LCSC Part #"] == ("" if c["lcsc"] == "UNKNOWN" else c["lcsc"]), mpn
        checked += bool(eq)
    assert checked == sum(1 for c in sourcing["parts"].values() if c.get("lcsc_equivalent"))


def test_drc_evidence_when_present_is_current():
    rep = ROOT / "reports/budget-2s/drc.json"
    ev = ROOT / "reports/budget-2s/drc-evidence.json"
    if not rep.exists():
        pytest.skip("budget board not routed")
    e = json.loads(ev.read_text(encoding="utf-8"))
    assert e["report_sha256"] == evidence.sha256_file(rep)
    for rel, digest in e["inputs"].items():
        assert evidence.sha256_file(ROOT / rel) == digest, rel
